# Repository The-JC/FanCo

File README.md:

# FanCo

FanCo is an advanced wind tunnel fan controller. Monitoring and regulating up to 120 fans individually with its custom UI or the API. 
The UI navigation is simple and intuitive utilizing just a rotary encoder.
FanCo is also capable of logging fan speeds over a longer period for later analyzation. 

FanCo is made up of two fundamental components. The master managing the UI and logging. And second, the slave, measuring actual speeds and compensate fluctuations in speed. Each Slave is capable of regulating up to 4 fans. Further slaves can be connected via cables to expand the maximum amounts of fans and also remove the number of control cables needed. 

## Table of contents
- [Requirements](#Requirements)
- [Installation](#Installation)
- [Usage](#Usage)
- [Principle of operation](#Principle%20of%20operation)
- [Troubleshooting](#Troubleshooting)
- [ToDo](#ToDo)

## Requirements
- RaspberryPi Zero (W) or 1 (2 or later only works with custom build)
- Slave PCB manufactured and soldered from your favorite Chinese manufacturer (see [Parts List](/circuits/slave/bom.pdf)).
- USBasp programmer (An Arduino can be used as a programmer).
- Any HDMI compatible display (we used a small 5" HDMI display)
- A rotary encoder as an input
- One or more 4-pin fans
- A 5V power supply to provide power to the Raspberry Pi and the Display

## Installation
### I. RaspberryPi  
1. Download the latest Raspbian Version from https://www.raspberrypi.org/downloads/ and flash it to the SD card.
2. Insert SD card into the pi. Start it check if it boots.
3. Run ```sudo apt-get update & upgrade ``` to update all packages.
4. Make sure you've downloaded and installed pigpiod from http://abyz.me.uk/rpi/pigpio/download.html.
5. Download the latest version of FanCoUI from  
https://github.com/The-JC/Rflw/releases/latest
    > You can use ```wget``` to directly download the binary to the RaspberryPi.
6. To run the FanCo UI run ```./fanco``` in the installation directory.
7. When using an 800x480 display change or add the following lines in  
**/boot/config.txt**
    ```
    hdmi_group=2
    hdmi_mode=87
    hdmi_cvt=800 480 60 0 0 0
    ```
8. To autostart FanCoUI at boot. Add the following lines to your rc.local before the exit 0 line.
```sudo nano /etc/rc.local```
    ```
    pigpiod
    PATH_TO_FANCO/fanco
    ```

### II. Slave
> **Requirments**  
>You will need [avrdude](http://www.nongnu.org/avrdude/) for flashing the program to the Slaves.
>Also you will need avr-gcc installed to compile the program.
>Further the build system CMake and make is required.
>You can install both on Ubuntu or Debian by running ```sudo apt-get install avrdude gcc-avr```
1. Connect the programmer and the slave, like shown in the following picture

2. Connect the programmer to the computer.
3. Change your current directory to ```cd programs/slave/FanRegulator_v01```
4. Change the slave address line ```#define ADDRESS 0xXX``` in ```include/config.h``` starting with 0x04
5. Configure the build by running ```cmake -B build .``` in the root directory of *FanRegulator_v01*
6. Go to the build directory by running ```cd build```
7. Run the following command to compile the program and flash it to the microcontroller: ```make flash```
8. Repeat the previous steps for every other microcontroller only changing the I2C address.

>**NOTE:** Currently only a USBasp programmer is the supported. We´re are working on supporting other programmer types like ArduinoISP. If you can't wait, you could also flash the binaries manualy using avrdude.

### III. Cabling
- Connect the rotary encoder, slave(s) and the display to the Raspberry Pi following the below scheme.

## Usage
1. Run ```sudo pigpiod```
2. Start program by running ```./fanco```

## Principle of operation
The slave counts pulses(n) received on the tacho pin in a set interval(dt). By calculating f=n/dt you`ll get the frequency(f) of the input signal. Further multiplication x60 converts the frequency from 1/t in s to min which equals RPMs (revolutions per minute).
Previously calculated speed is used for fine-tuning the fans set signal, to achieve a steady and constant speed at the desired speed.  
Further, the acquired data is requested by the master (RaspberyPi) every second. For logging, displaying and synchronization purposes.  
Firstly it´s averaged out to compensate for measurement and transmission errors. It later gets stored for logging and plotting purposes.

## Troubleshooting
#### Rotary Encoder is not recognized
- Check if cables are connected correctly
- Make sure you have pull-up resistors on all 3 data lines

#### FanCoUI shows invalid or random data
- Make sure all slaves are powered up
- Check the data bus for wiring errors
- Check if all slaves are recognized by running ```i2cdetect -y 1```
- Try running ```i2cdump -y -r 0-2 1 0x04 c```
    - Reading devices fails -> restart all slaves & try updating slaves
    - Reads X X X as byte-value -> restart all slaves
    - Reads some byte-value -> all should be good try updating FanCoUI to the latest version.

## ToDo
- Interval programming
- Extended logs
- Remote control API
- init.d start script
- Enclosure
- Flow dependent speed control

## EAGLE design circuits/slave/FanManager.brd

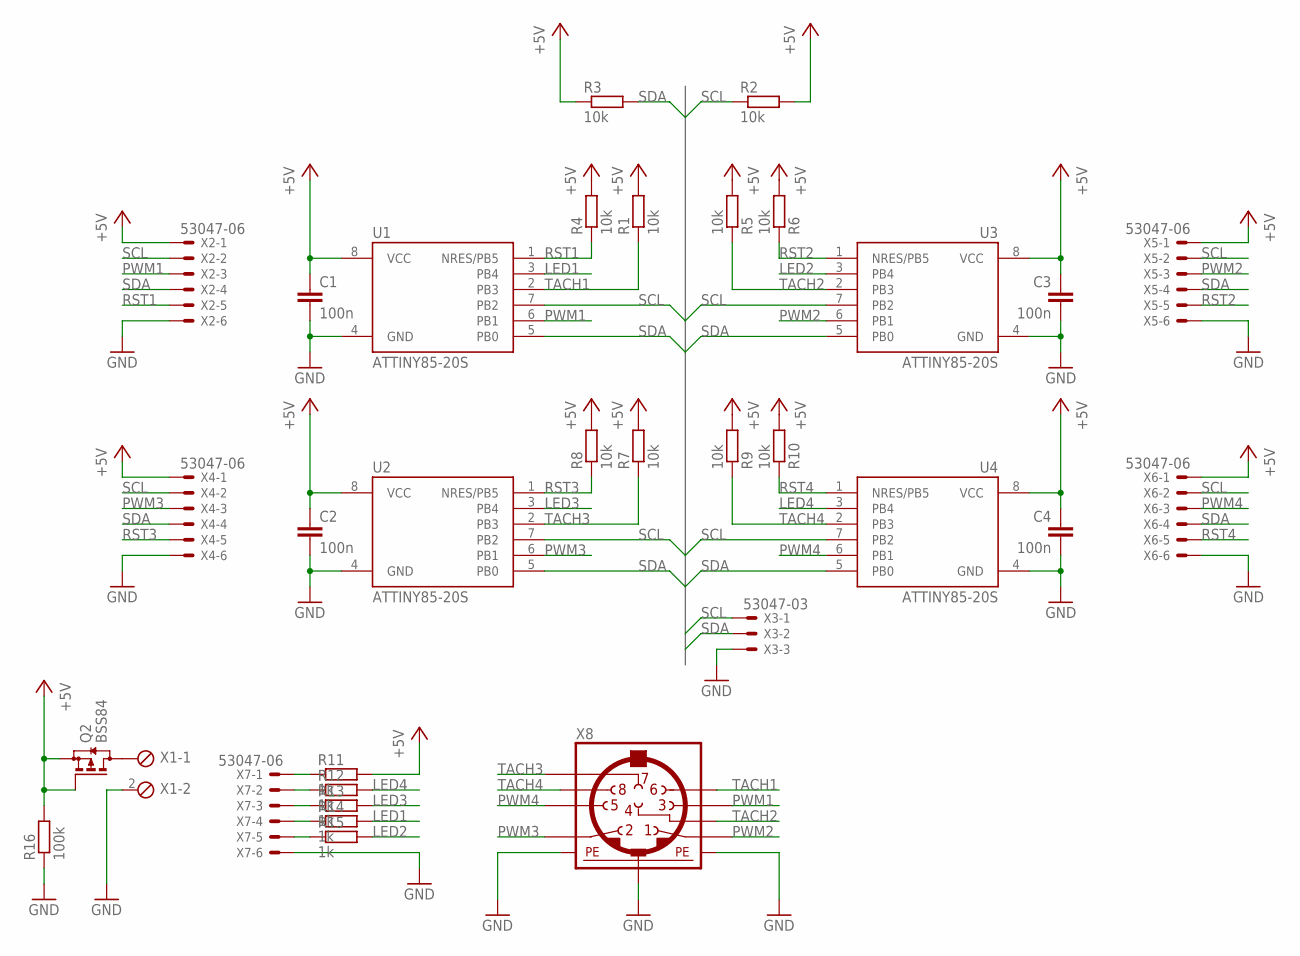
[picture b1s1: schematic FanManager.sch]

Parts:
C1, C2, C3, C4: 100n; C0805
Q2: BSS84; SOT23
R1, R2, R3, R4, R5, R6, R7, R8, R9, R10: 10k; R0805
R11, R12, R13, R14, R15: 1k; R0805
R16: 100k; R0805
U1, U2, U3, U4: ATTINY85-20S; SOIC8_EIAJ_208MIL
X1: KLEMME_2XRAND_LANGPAD; 2POL254
X2, X4, X5, X6, X7: 53047-06
X3: 53047-03
X8: MINI_DIN_8; M_DIN8

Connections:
+5V: C1.1, C2.1, C3.1, C4.1, Q2.1 (G), Q2.2 (S), R1.2, R2.2, R3.1, R4.2, R5.2, R6.2, R7.2, R8.2, R9.2, R10.2, R11.2, R16.2, U1.8 (VCC), U2.8 (VCC), U3.8 (VCC), U4.8 (VCC), X2.1, X4.1, X5.1, X6.1
GND: C1.2, C2.2, C3.2, C4.2, R16.1, U1.4 (GND), U2.4 (GND), U3.4 (GND), U4.4 (GND), X1.2, X2.6, X3.3, X4.6, X5.6, X6.6, X7.6, X8.SH1 (PE1), X8.SH2 (PE2), X8.SH3 (PE3)
LED1: R14.2, U1.3 (PB4)
LED2: R15.2, U3.3 (PB4)
LED3: R13.2, U2.3 (PB4)
LED4: R12.2, U4.3 (PB4)
unnamed: Q2.3 (D), X1.1
unnamed: R11.1, X7.1
unnamed: R12.1, X7.2
unnamed: R13.1, X7.3
unnamed: R14.1, X7.4
unnamed: R15.1, X7.5
PWM1: U1.6 (PB1), X2.3, X8.3
PWM2: U3.6 (PB1), X5.3, X8.1
PWM3: U2.6 (PB1), X4.3, X8.2
PWM4: U4.6 (PB1), X6.3, X8.5
RST1: R4.1, U1.1 (NRES/PB5), X2.5
RST2: R6.1, U3.1 (NRES/PB5), X5.5
RST3: R8.1, U2.1 (NRES/PB5), X4.5
RST4: R10.1, U4.1 (NRES/PB5), X6.5
SCL: R2.1, U1.7 (PB2), U2.7 (PB2), U3.7 (PB2), U4.7 (PB2), X2.2, X3.1, X4.2, X5.2, X6.2
SDA: R3.2, U1.5 (PB0), U2.5 (PB0), U3.5 (PB0), U4.5 (PB0), X2.4, X3.2, X4.4, X5.4, X6.4
TACH1: R1.1, U1.2 (PB3), X8.6
TACH2: R5.1, U3.2 (PB3), X8.4
TACH3: R7.1, U2.2 (PB3), X8.7
TACH4: R9.1, U4.2 (PB3), X8.8

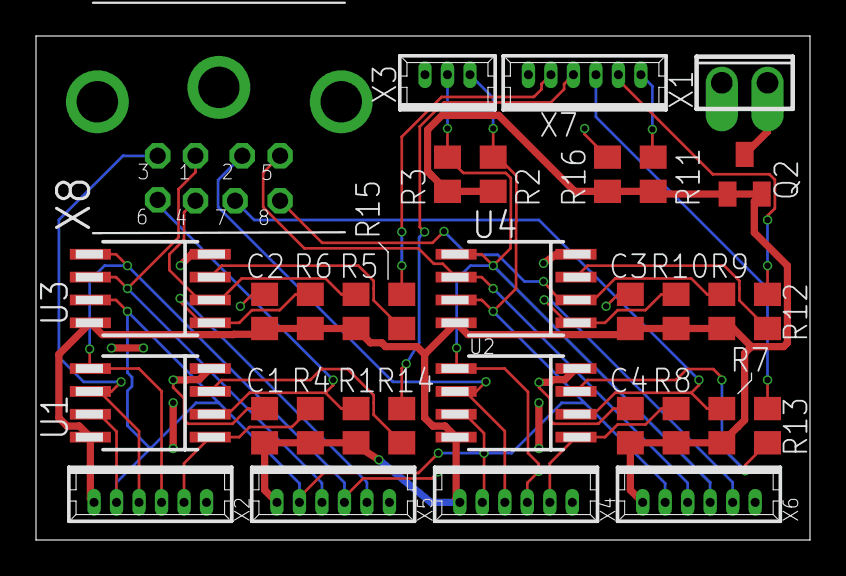
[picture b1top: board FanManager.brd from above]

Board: 2 copper layers, 43.0 x 28.0 mm, 33 parts (0 on the bottom side), 26 nets.

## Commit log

2019-09-25 init
2019-10-01 added adjustable pwm frequenz and updated config file
2019-10-06 fixed i2c interrupt bug
2019-10-24 improved PID regulation and fixed overflow-bug, added getDuCy for CSV-file, removed setOvf
2019-10-26 added circuits and step_response program and assorted these
2019-12-09 implemented frontend
2019-12-09 removed useless install file
2019-12-09 added XD design
2019-12-10 Implemented simple backend API
2019-12-12 I2C fan readout in API
2019-12-12 Error Handler Implemented error handling. Also included buttonHandler & encoderHandler for easier usage with alternative inputs.
2019-12-31 updated refresh-speed using Timer1 compare-interrupt
2019-12-31 correct error in config file
2020-01-06 Qt instead of NodeJs&Python
    frontend and backend replaced with native Qt application.
2020-01-08 Schematic and board PDF
2020-01-12 added documentation in hedaer files and use compare interrupt instead of ovf
2020-01-16 Hold, short and long button press
2020-01-16 Set speed implemted
2020-01-17 Button press switch
2020-01-19 Update README.md (cabling and corrections)
2020-01-19 Moved headers to include directory
2020-01-19 Added CMake to compile FanRegulator
2020-01-19 Update README.md (Slave installation)
2020-01-20 README.md table of contents & notes
2020-03-02 Popup
2020-09-17 Minor optimizations
    - Changed C type casts to C++ type
    - Fixed overflow due to wrong data type
2020-09-17 Add Codacy badge

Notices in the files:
circuits/slave/FanManager.brd:
© 2019
